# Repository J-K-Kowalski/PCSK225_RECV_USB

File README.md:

# PCSK225 RECEIVER WITH USB
## eCzas Radio PCSK-225 - Timeframe Receiver with USB

<ul>
<li>2024-07-25 - First version of the project</li>
</ul>

<p>Based on a receiver made of <a href="https://github.com/e-CzasPL/TimeReceiver225kHz" target="_blank">e-CzasPL Radio</a> I have developed a test receiver with a built-in serial/USB converter and a simple antenna amplifier on one transistor. The design is made in KiCAD 8.
</p>

<p>Receiver contains three basic blocks
<ol>
<li>USB interface on FT230X + LDO 3.3V
<li>DSPic33FJ128 processor with optional TCXO generator and PicDIV divider
<li>Radio interface on Si4735 chip with antenna amplifier on FET transistor
</ol> 

<b>NOTE</b> - The firmware comes from the eCzasPL project. I don't have the source codes.

### USB interface

<p>I built the USB interface on the FT230XS chip, one of the simplest serial/USB chips. I used a USB-C 2.0 connector for data transfer and a 5V power supply.
<p>To protect the circuit against reverse polarity (and such things happen in experiments), I used the Q2 transistor. Resistors R2 R3 inform the host computer that 5V is required. LED7 and LED8 show the transmission status.
<p> The U3 chip is a simple LDO with an output voltage of 3.3V. The whole circuit consumes about 100mA. This regulator, with a significant excess, provides such a current intensity. The external 3.3V power connector (when USB and LDO are not mounted) is protected by the Q4 transistor. The additional input of the 5V power supply is protected only by diode D1.

### DSPic33FJ128 processor

<p>Based on the eCzas original project, I used the DSPIC33FJ128MC804-PT processor indicated in the eCzasPL projections in an easy (relatively) manual mount housing. As standard, I included 100nF blocking capacitors on the appropriate pins, I2C pull-up resistors, and a quartz generator on a typical 10MHz quartz. The LED1 - LED4 LED set signals the status of the receiver. The device has two serial interfaces: NMEA and TEST. 
<p>The NMEA interface on pin (1) of the connector sends an NMEA frame $GPRMC - which allows the use of standard libraries available for microcontrollers and computers for time decoding. The second output, TEST on pin (3), sends information about the state of the chip in text form. Both interfaces operate at a speed of 115200 baud.
<p>Optionally, a high-precision TCXO generator can be installed, which generates a frequency of 10MHZ and can power the CPU clock. This significantly increases the accuracy of the work. To obtain a 1PPS signal, a PIC12F675 chip is used (in two versions of the housing, of course, only one of them needs to be installed). PICDIV source: http://www.leapsecond.com/pic/picdiv.htm, assembler & build-instructions: https://github.com/aewallin/PICDIV.

<p> NOTE - micro-stepping and PICDIV synchronization still need to be implemented in the eCzasPL Radio firmware.

### HF Receiver

<p>Ferrite antenna, e.g., from https://telzam.pl/anteny-dcf/ (also made by antennas at 225kHz), is connected via the ANT0 connector to the FET transistor, which acts as an amplifier. It is optional, and it is possible to short-circuit the appropriate JP2 fields so that the signal reaches the input of the Si4735 chip directly. This circuit is combined with a 32kHz watch quartz, which, using the SSB patch, allows for a mixed sideband frequency (upper USB) of 1kHz. This signal obtained from the LOUT output is amplified in a single-stage U$1A amplifier, and the signal feeds the processor's ADC. I used the second amplifier of the U$1B circuit as a 1kHz signal comparator.

### Output signals

<p>The NMEA output should have data as shown below. After getting synchronized, it appears every 1 minute. In frame $PGGUM, the first 9 bytes are the same as the encoded time frame, and the last is the time since the last received valid frame. An RMC (Recommended Minimum Specific GNSS Data) frame was used to synchronize the time. The receiver does not know its geographical location, so for compatibility with GNSS receivers, static coordinates are sent in the frame <a href="https://www.google.pl/maps/place/52%C2%B014'30.6%22N+21%C2%B000'03.0%22E/@52.24183,20.9982597,17z/data=!3m1!4b1!4m4!3m3!8m2!3d52.24183!4d21.00084?entry=ttu" target=_blank>Laboratory of Time and Frequency of the Central Office of Measures in Warsaw (52.24183N,  21.00084E)</a>.

<p>A detailed description is provided in <a href="https://github.com/e-CzasPL/TimeReceiver225kHz/blob/main/doc/e-CzasPL-Opis-projektu-przykladowego-modulu-odbiorczego-e-Czas-Radio.pdf">documentation</a> on page 8.

<p>

<p> On the TEST output, the system sends diagnostic data. STS: MAX/MIN - maximum and minimum level with ADC (12 bit) - can help optimize the 1 kHz audio level per CPU input. IIR - is "offset" - shifting the 1kHz fringe - from the nominal frequency, showing the "detuning" of the front end - controlled by this small quartz.  This allows the DSP filter to keep up with the usable signal. 
<p>

## LED Signals
<ul>
<li>LED1 - DCD Blue - signaling of recognition of the beginning of the data frame (after the keyword is detected) – remains lit until the end of the frame transmission,
<li>LED2 - RTC Green - Informs about receiving the correct time and entering it into the RTC, if it is not possible to update the RTC from the radio transmission, the diode is turned off after 24 hours,
<li>LED3 - PPS Yellow - 1PPS 1PPS signal synchronized with the received time signal,
<li>LED4 - FRM Orange - lit after the correct reception of the data frame, calculation of correction codes and confirmation of data correctness. The rising edge informs about the beginning of the second (transmitted in the data frame).
</ul>

# PCSK225 ODBIORNIK Z USB
## eCzas Radio PCSK-225 - Odbiornik ramki czasu z USB

<p> Na bazie odbiornika uroszczonego z <a href="https://github.com/e-CzasPL/TimeReceiver225kHz" target="_blank">e-CzasPL Radio</a> opracowałem testowy odbiornik z wbudowanym konwerterem serial/USB oraz prostym wzmacniaczem antenowym na jednym tranzystorze. Projekt jest wykonany w KiCAD 8.
</p>

<p>Odbiornik zawiera trzy podstawowe bloki
<ol>
<li>Interfejs USB na układzie FT230X + LDO 3.3V
<li>Procesor DSPic33FJ128 wraz z opcjonalnym generatorem TCXO i dzielnikiem PicDIV
<li>Interfejsem radiowym na układzie Si4735 ze wzmacniaczem antenowym na tranzystorze FET
</ol>

<b>UWAGA</b> - Firmware pochodzi z projektu eCzasPL, nie posiadam kodów źródłowych

### Interfejs USB

<p>Interfejs USB zbudowałem na układzie FT230XS, jednym z najprostszych układów typu serial/USB. Zastosowałem typowe złącze USB-C 2.0 do przesyłania danych i zasilania napięciem 5V.
<p>Do zabezpieczenia układu przed odwrotną polaryzacją (a takie rzeczy się zdarzają przy eksperymentach) zastosowałem tranzystor Q2. Rezystory R2, R3 informują komputer hosta że wymagane jest napięcie 5V. stan transmisji pokazują diody LED7 i LED8.
<p> Układ U3 jest prostym LDO o napięciu wyjściowym 3.3V. Cały układ pobiera ok 100mA, ten stabilizator z dużym  nadmiarem zapewnia takie natężenie prądu. Złącze zewnętrznego zasilania 3.3V (gdy nie jest zamontowany USB i LDO) jest zabezpieczone tranzystorem Q4. Wejście dodatkowe zasilania 5V zabezpieczone jest tylko diodą D1.

### Procesor DSPic33FJ128

<p>W układzie zastosowałem wskazany w projekcje eCzasPL procesor DSPIC33FJ128MC804-PT w łatwej (stosunkowo) do montażu ręcznego obudowie. Standardowo dołączyłem kondensatory blokujące 100nF na odpowiednich pinach, rezystory podciągające I2C, generator kwarcowy na typowym kwarcu 10MHz. Zestaw ledów LED1 - LED4 sygnalizuje status odbiornika. Układ ma dwa interfejsy szeregowe: NMEA i TEST. 
<p>Interfejs NMEA na pinie (1) złącza wysyła ramkę NMEA $GPRMC - co pozwoliło na stosowania do dekodowania czasu standardowych bibliotek dostępnych dla mikrokontrolerów i komputerów. Drugie wyjście TEST na pinie (3) wysyła informacje o stanie układu w postaci tekstowej. Obydwa interfejsy pracują w szybkości 115200 bodów.
<p>Opcjonalnie można zamontować precyzyjny generator TCXO który generuje częstotliwość 10MHZ i może zasilać zegar procesora. Znacznie zwiększa to dokładność pracy. W celu uzyskania sygnału 1PPS zastosowano układ PIC12F675 (w dwóch wersjach obudowy, oczywiście nalezy zamontować tylko jeden z nich). Kod źródłowy PICDIV: http://www.leapsecond.com/pic/picdiv.htm, assembler & build-instructions: https://github.com/aewallin/PICDIV.
	
<p> UWAGA - microsteping i synchronizacja PICDIV nie jest jeszcze zaimplementowana w firmware eCzasPL Radio.

### Odbiornik HF

<p>Antena ferrytowa np. z https://telzam.pl/anteny-dcf/ (wykonują także anteny na 225kHz) podłączona jest przez złącze ANT0 do tranzystora FET który pełni rolę wzmacniacza. Jest on opcjonalny i można zewrzeć odpowiednie pola JP2 aby sygnał docierał bezpośrednio do wejścia układu Si4735. Układ ten jest połączony z kwarcem zegarkowym 32kHz, co przy użyciu patcha SSB pozwala na uzyskanie zmieszanej częstotliwości wstęgi bocznej (górnej USB) o częstotliwości 1kHz. Ten sygnał uzyskiwany z wyjścia LOUT jest wzmacniany w jednostopniowym wzmacniaczu U$1A i sygnał zasila przetwornik ADC w procesorze. Drugi wzmacniacz układu U$1B użyłem jako komparator sygnału 1kHz.

### Sygnały wyjściowe

<p>Na wyjściu NMEA powinny byc dane jak pokazano poniżej. Po uzyskaniu synchronizacji pojawia się co 1min. ramka $PGGUM, pierwsze 9 bajtów to kojejne bajty zakodowanej ramki czasu, ostatni to czas od ostatnio odebranej poprawnej ramki. Do synchronizacji czasu zastosowano ramkę RMC (Recommended Minimum Specific GNSS Data). Odbiornik nie zna swojego położenia geograficznego, dlatego dla zachowania kompatybilności z odbiornikami GNSS w ramce przesyłane są statyczne współrzędne <a  href="https://www.google.pl/maps/place/52%C2%B014'30.6%22N+21%C2%B000'03.0%22E/@52.24183,20.9982597,17z/data=!3m1!4b1!4m4!3m3!8m2!3d52.24183!4d21.00084?entry=ttu" target=_blank>Laboratorium Czasu i Częstotliwości Głównego Urzędu Miar w Warszawie (52.24183N, 21.00084E)</a>.

<p>Dokładny opis zawarty jest w <a href="https://github.com/e-CzasPL/TimeReceiver225kHz/blob/main/doc/e-CzasPL-Opis-projektu-przykladowego-modulu-odbiorczego-e-Czas-Radio.pdf">dokumentacji</a>  na stronie 8.

<p>

<p> Na wyjściu TEST układ wysyła dane diagnostyczne. STS: MAX/MIN - maksymalny i minimalny poziom z ADC (12 bitów) - może być pomocny przy optymalizacji poziomu audio 1 kHz na wejście procesora. IIR - to "offset" - przesunięcie prążka 1kHz - od częstotliwości nominalnej, pokazuje "odstrojenie" frontendu - sterowanego tym kwarcem zegarkowym.  Umożliwia to nadążenie filtrem DSP za sygnałem użytecznym. 
<p>

## Sygnały LED
<ul>
<li>LED1 - DCD Blue - sygnalizacja rozpoznania początku ramki danych (po wykryciu słowa kluczowego) – pozostaje zapalona do końca transmisji ramki,
<li>LED2 - RTC Green - Informuje o odebraniu poprawnego czasu i wpisaniu go do RTC, w przypadku braku możliwości aktualizacji RTC z transmisji radiowej dioda jest gaszona po 24 godzinach,
<li>LED3 - PPS Yellow - 1PPS Sygnał 1PPS zsynchronizowany z odebranym sygnałem czasu,
<li>LED4 - FRM Orange - zapalana po poprawnym odebraniu ramki danych, przeliczeniu kodów korekcyjnych oraz potwierdzeniu poprawności danych. Narastające zbocze informuje o początku sekundy (przesłanej w ramce danych).
</ul>

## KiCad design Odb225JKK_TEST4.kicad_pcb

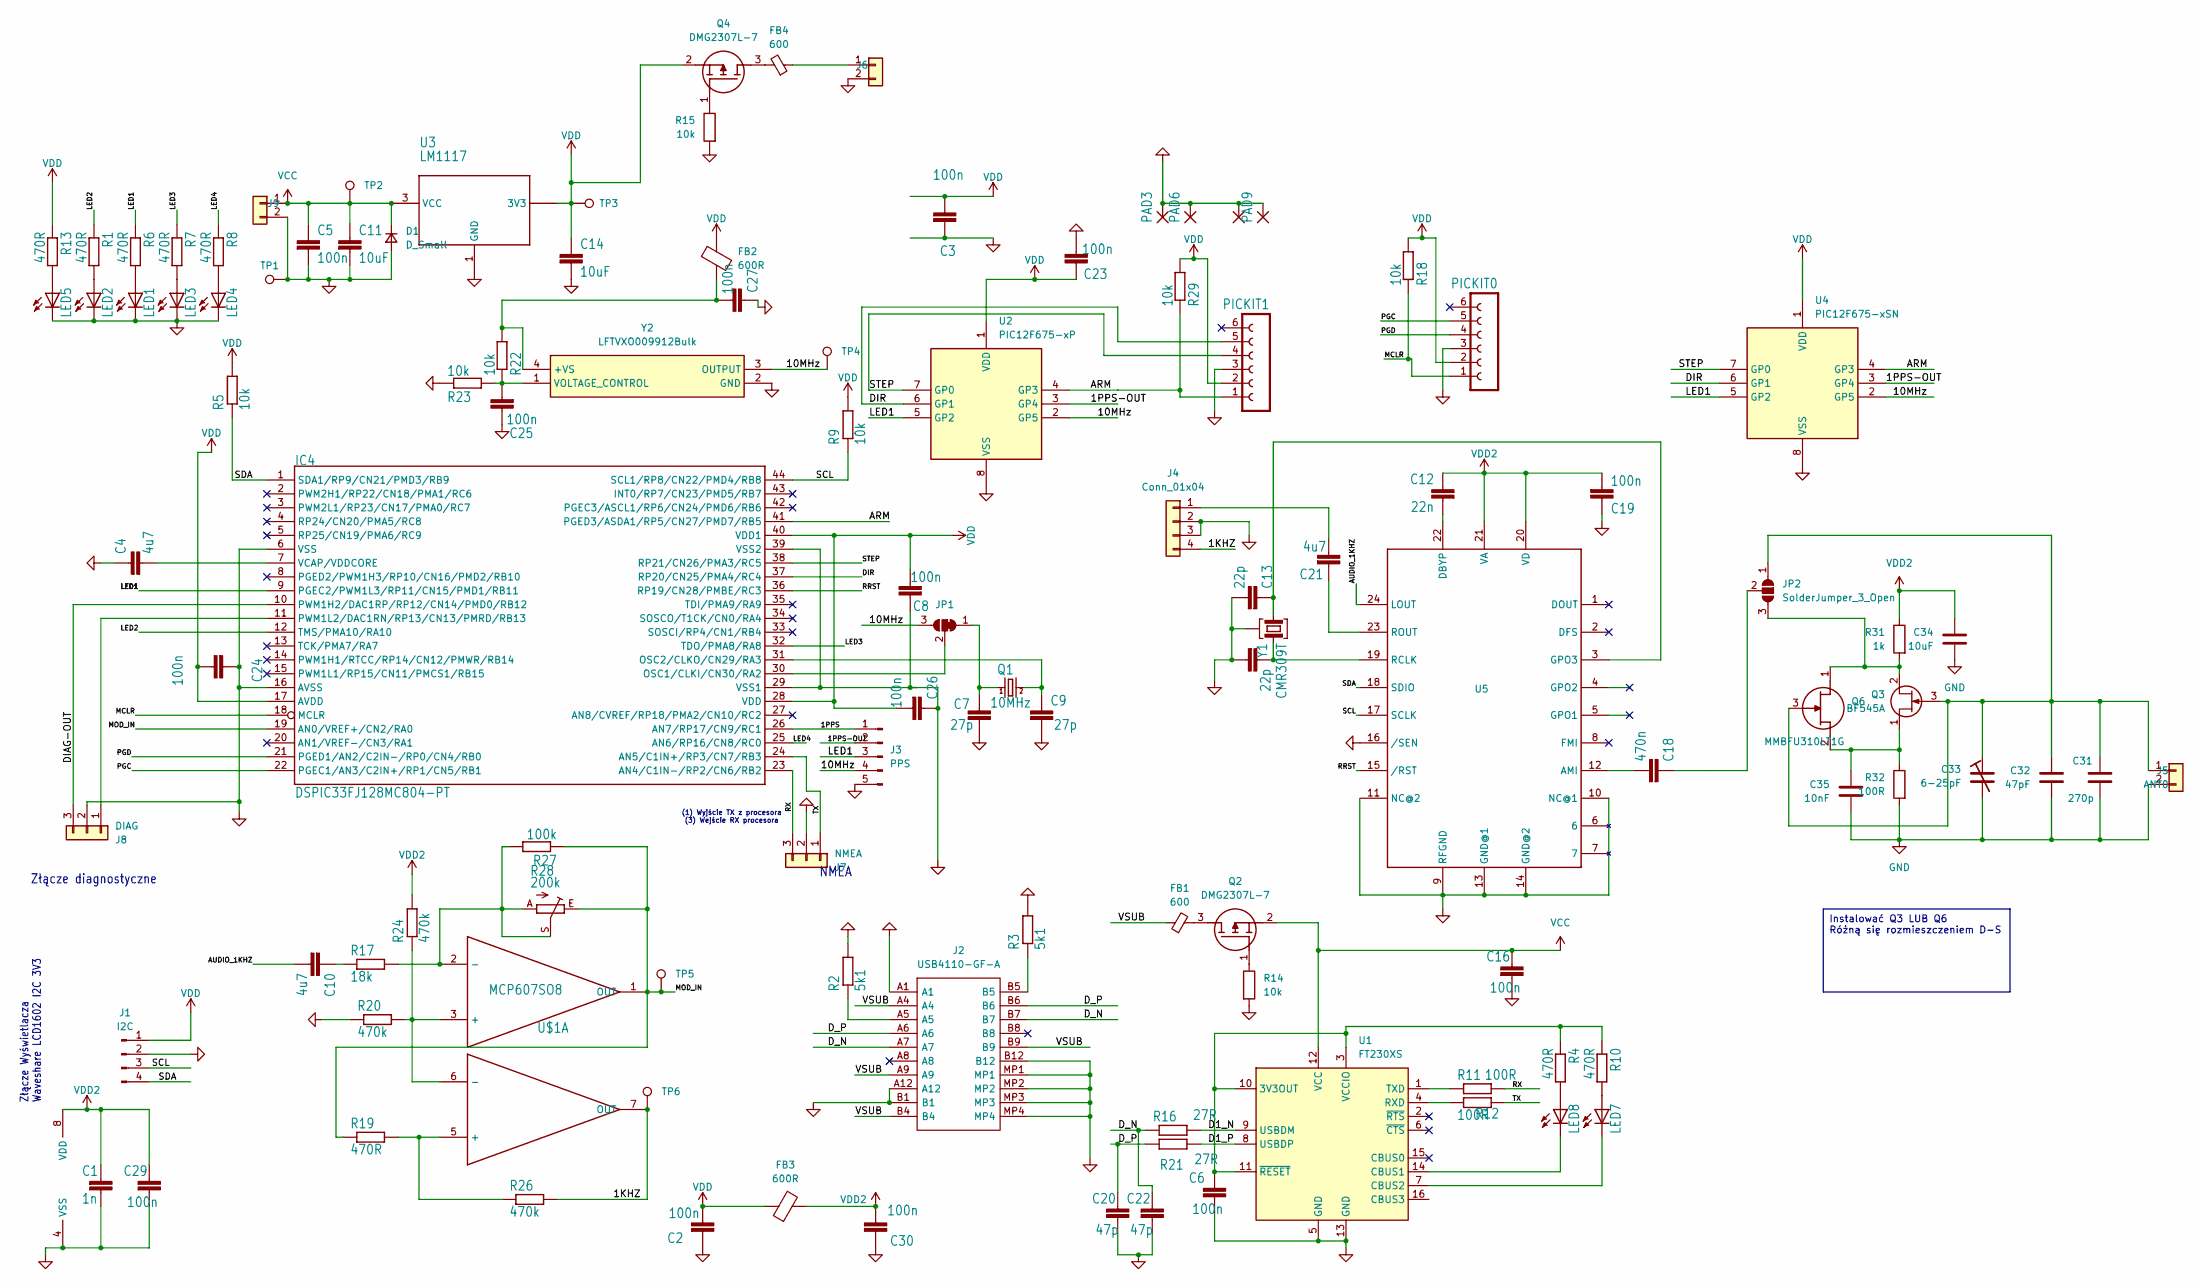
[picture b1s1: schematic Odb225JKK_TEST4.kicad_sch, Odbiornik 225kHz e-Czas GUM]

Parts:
C1: 1n; C_0603_1608Metric_Pad1.08x0.95mm_HandSolder
C2, C3, C5, C6, C8, C16, C19, C23, C24, C26, C27, C29, C30: 100n; C_0603_1608Metric_Pad1.08x0.95mm_HandSolder
C4, C10, C21: 4u7; C_0603_1608Metric_Pad1.08x0.95mm_HandSolder
C7, C9: 27p; C_0603_1608Metric_Pad1.08x0.95mm_HandSolder
C11, C14, C34: 10uF; C_0603_1608Metric_Pad1.08x0.95mm_HandSolder
C12: 22n; C_0603_1608Metric_Pad1.08x0.95mm_HandSolder
C13, C15: 22p; C_0603_1608Metric_Pad1.08x0.95mm_HandSolder
C18: 470n; C_0603_1608Metric_Pad1.08x0.95mm_HandSolder
C20, C22: 47p; C_0603_1608Metric_Pad1.08x0.95mm_HandSolder
C25: 100n; C0603K
C31: 270p; C_0603_1608Metric_Pad1.08x0.95mm_HandSolder
C32: 47pF; C_0603_1608Metric_Pad1.08x0.95mm_HandSolder
C33: 6-25pF; C_Trimmer_Murata_TZB4-B
C35: 10nF; C_0603_1608Metric_Pad1.08x0.95mm_HandSolder
D1: D_Small; D_1206_3216Metric_Pad1.42x1.75mm_HandSolder
FB1, FB4: 600; C0603K
FB2, FB3: 600R; C_0603_1608Metric_Pad1.08x0.95mm_HandSolder
IC4: DSPIC33FJ128MC804-PT; TQFP44
J1: I2C; PinHeader_1x04_P2.54mm_Vertical
J2: USB4110-GF-A; USB4110GFA; Mouser Part Number 640-USB4110-GF-A
J3: PPS; PinHeader_1x05_P2.54mm_Vertical
J4: Conn_01x04; PinHeader_1x04_P2.54mm_Vertical
J5, J6, J9: ANT0; PinHeader_1x02_P2.54mm_Vertical
J7: NMEA; PinHeader_1x03_P2.54mm_Vertical
J8: DIAG; PinHeader_1x03_P2.54mm_Vertical
JP1: SolderJumper_3_Bridged12; SolderJumper-3_P1.3mm_Bridged12_RoundedPad1.0x1.5mm
JP2: SolderJumper_3_Open; SolderJumper-3_P1.3mm_Open_RoundedPad1.0x1.5mm
LED1, LED2, LED3, LED4, LED5, LED7, LED8: LEDCHIPLED_0805; CHIP-LED0805
PAD3, PAD6, PAD8, PAD9: 1,6/0,9; 1,6_0,9
PICKIT0, PICKIT1: FE06-1; PinHeader_1x06_P2.54mm_Vertical
Q1: 10MHz; HC49U-V
Q2, Q4: DMG2307L-7; SOT96P240X110-3N; Mouser Part Number 621-DMG2307L-7
Q3: BF545A; SOT-23
Q6: MMBFU310LT1G; SOT96P237X111-3N; Mouser Part Number 863-MMBFU310LT1G
R1, R4, R6, R7, R8, R10, R13, R19: 470R; R_0603_1608Metric_Pad0.98x0.95mm_HandSolder
R2, R3: 5k1; R_0603_1608Metric_Pad0.98x0.95mm_HandSolder
R5, R9, R14, R15, R18, R22, R23, R29: 10k; R_0603_1608Metric_Pad0.98x0.95mm_HandSolder
R11, R12, R32: 100R; R_0603_1608Metric_Pad0.98x0.95mm_HandSolder
R16, R21: 27R; R_0603_1608Metric_Pad0.98x0.95mm_HandSolder
R17: 18k; R_0603_1608Metric_Pad0.98x0.95mm_HandSolder
R20, R24, R26: 470k; R_0603_1608Metric_Pad0.98x0.95mm_HandSolder
R27: 100k; R_0603_1608Metric_Pad0.98x0.95mm_HandSolder
R28: 200k; RJ9W
R31: 1k; R_0603_1608Metric_Pad0.98x0.95mm_HandSolder
TP1, TP2, TP3, TP4, TP5, TP6: TestPoint; TestPoint_Pad_D1.5mm
U1: FT230XS; SSOP-16_3.9x4.9mm_P0.635mm
U2: PIC12F675-xP; DIP-8_W7.62mm
U3: LM1117; SOT223-3
U4: PIC12F675-xSN; SOIC-8_3.9x4.9mm_P1.27mm
U5: SI4735-D60; SSOP24
U$1: MCP607SO8; SOIC8
Y1: CMR309T
Y2: LFTVXO009912Bulk; Mouser Part Number 449-LFTVXO009912BULK

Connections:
/1KHZ: J4.4, R26.2, TP6.1, U$1.7 (OUT)
/1PPS: IC4.26 (AN7/RP17/CN9/RC1), J3.1
/1PPS-OUT: J3.2, U2.3 (GP4), U4.3 (GP4)
/10MHz: J3.4, JP1.3 (B), TP4.1, U2.2 (GP5), U4.2 (GP5), Y2.3 (OUTPUT)
/ARM: IC4.41 (PGED3/ASDA1/RP5/CN27/PMD7/RB5), PICKIT1.1, R29.1, U2.4 (GP3), U4.4 (GP3)
/AUDIO_1KHZ: C10.2, U5.24 (LOUT)
/D1_N: R16.2, U1.9 (USBDM)
/D1_P: R21.2, U1.8 (USBDP)
/DIAG-OUT: IC4.10 (PWM1H2/DAC1RP/RP12/CN14/PMD0/RB12), J8.3
/DIR: IC4.37 (RP20/CN25/PMA4/RC4), PICKIT1.5, U2.6 (GP1), U4.6 (GP1)
/D_N: C22.1, J2.A7, J2.B7, R16.1
/D_P: C20.1, J2.A6, J2.B6, R21.1
/LED1: IC4.9 (PGEC2/PWM1L3/RP11/CN15/PMD1/RB11), J3.3, R6.1, U2.5 (GP2), U4.5 (GP2)
/LED2: IC4.12 (TMS/PMA10/RA10), R1.1
/LED3: IC4.32 (TDO/PMA8/RA8), R7.1
/LED4: IC4.25 (AN6/RP16/CN8/RC0), R8.1
/MCLR: IC4.18 (MCLR), PICKIT0.1, R18.1
/MOD_IN: IC4.19 (AN0/VREF+/CN2/RA0), R19.1, R27.1, R28.E, TP5.1, U$1.1 (OUT)
/PGC: IC4.22 (PGEC1/AN3/C2IN+/RP1/CN5/RB1), PICKIT0.5
/PGD: IC4.21 (PGED1/AN2/C2IN-/RP0/CN4/RB0), PICKIT0.4
/RRST: IC4.36 (RP19/CN28/PMBE/RC3), U5.15 (/RST)
/RX: IC4.23 (AN4/C1IN-/RP2/CN6/RB2), J7.3, R11.2
/SCL: IC4.44 (SCL1/RP8/CN22/PMD4/RB8), J1.3, R9.1, U5.17 (SCLK)
/SDA: IC4.1 (SDA1/RP9/CN21/PMD3/RB9), J1.4, R5.1, U5.18 (SDIO)
/STEP: IC4.38 (RP21/CN26/PMA3/RC5), PICKIT1.4, U2.7 (GP0), U4.7 (GP0)
/TX: IC4.24 (AN5/C1IN+/RP3/CN7/RB3), J7.1, R12.2
/VSUB: FB1.1, J2.A4, J2.A9, J2.B4, J2.B9
GND: C1.2, C2.2, C3.2, C4.1, C5.2, C6.2, C7.2, C8.1, C9.2, C11.2, C13.2, C14.2, C15.1, C16.2, C19.1, C20.2, C22.2, C23.2, C24.1, C25.1, C26.1, C27.1, C29.2, C30.2, C31.2, C32.2, C33.2, C34.2, C35.2, D1.2 (A), IC4.6 (VSS), IC4.16 (AVSS), IC4.29 (VSS1), IC4.39 (VSS2), J1.2, J2.A1, J2.A12, J2.B1, J2.B12, J2.MP1, J2.MP2, J2.MP3, J2.MP4, J3.5, J4.2, J4.3, J5.2, J6.2, J7.2, J8.2, J9.2, LED1.C, LED2.C, LED3.C, LED4.C, LED5.C, PAD3.1, PAD6.1, PAD8.1, PAD9.1, PICKIT0.3, PICKIT1.3, R2.2, R3.2, R14.2, R15.2, R20.1, R23.1, R32.2, TP1.1, U1.5 (GND), U1.13 (GND), U2.8 (VSS), U3.1 (GND), U4.8 (VSS), U5.9 (RFGND), U5.10 (NC@1), U5.11 (NC@2), U5.13 (GND@1), U5.14 (GND@2), U5.16 (/SEN), U$1.4 (VSS), Y1.3 (G), Y2.2 (GND)
unnamed: C10.1, R17.1
unnamed: IC4.30 (OSC1/CLKI/CN30/RA2), JP1.2 (C)
unnamed: C9.1, IC4.31 (OSC2/CLKO/CN29/RA3), Q1.2
unnamed: IC4.11 (PWM1L2/DAC1RN/RP13/CN13/PMRD/RB13), J8.1
unnamed: C4.2, IC4.7 (VCAP/VDDCORE)
unnamed: J2.A5, R2.1
unnamed: J2.B5, R3.1
unnamed: C21.2, J4.1
unnamed: C31.1, C32.1, C33.1, J5.1, JP2.1 (A), Q3.3 (G), Q6.3 (G)
unnamed: FB4.1, J6.1
unnamed: C7.1, JP1.1 (A), Q1.1
unnamed: JP2.3 (B), Q3.2 (D), Q6.1 (D), R31.2
unnamed: C18.1, JP2.2 (C)
unnamed: LED1.A, R6.2
unnamed: LED2.A, R1.2
unnamed: LED3.A, R7.2
unnamed: LED4.A, R8.2
unnamed: LED5.A, R13.2
unnamed: LED7.A, R10.2
unnamed: LED8.A, R4.2
unnamed: FB1.2, Q2.3 (D)
unnamed: Q2.1 (G), R14.1
unnamed: C35.1, Q3.1 (S), Q6.2 (S), R32.1
unnamed: FB4.2, Q4.3 (D)
unnamed: Q4.1 (G), R15.1
unnamed: C6.1, R4.1, R10.1, U1.3 (VCCIO), U1.10 (3V3OUT), U1.11 (~RESET)
unnamed: LED8.C, U1.14 (CBUS1)
unnamed: LED7.C, U1.7 (CBUS2)
unnamed: R12.1, U1.4 (RXD)
unnamed: R11.1, U1.1 (TXD)
unnamed: C18.2, U5.12 (AMI)
unnamed: C12.2, U5.22 (DBYP)
unnamed: C13.1, U5.3 (GPO3), Y1.1
unnamed: C15.2, U5.19 (RCLK), Y1.2
unnamed: C21.1, U5.23 (ROUT)
unnamed: R20.2, R24.1, U$1.3 (+), U$1.6 (-)
unnamed: R17.2, R27.2, R28.A, R28.S, U$1.2 (-)
unnamed: R19.2, R26.1, U$1.5 (+)
unnamed: C27.2, FB2.2, R22.2, Y2.4 (+VS)
unnamed: C25.2, R22.1, R23.2, Y2.1 (VOLTAGE_CONTROL)
VCC: C5.1, C11.1, C16.1, D1.1 (K), J9.1, Q2.2 (S), TP2.1, U1.12 (VCC), U3.3 (VCC)
VDD: C2.1, C3.1, C8.2, C14.1, C23.1, C24.2, C26.2, FB2.1, FB3.1, IC4.17 (AVDD), IC4.28 (VDD), IC4.40 (VDD1), J1.1, PICKIT0.2, PICKIT1.2, Q4.2 (S), R5.2, R9.2, R13.1, R18.2, R29.2, TP3.1, U2.1 (VDD), U3.2 (3V3), U3.4 (3V3), U4.1 (VDD)
VDD2: C1.1, C12.1, C19.2, C29.1, C30.1, C34.1, FB3.2, R24.2, R31.1, U5.20 (VD), U5.21 (VA), U$1.8 (VDD)

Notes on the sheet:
Instalować Q3 LUB Q6 Różną się rozmieszczeniem D-S
Złącze diagnostyczne
(1) Wyjście TX z procesora (3) Wejście RX procesora
Złącze Wyświetlacza Waveshare LCD1602 I2C 3V3
NMEA

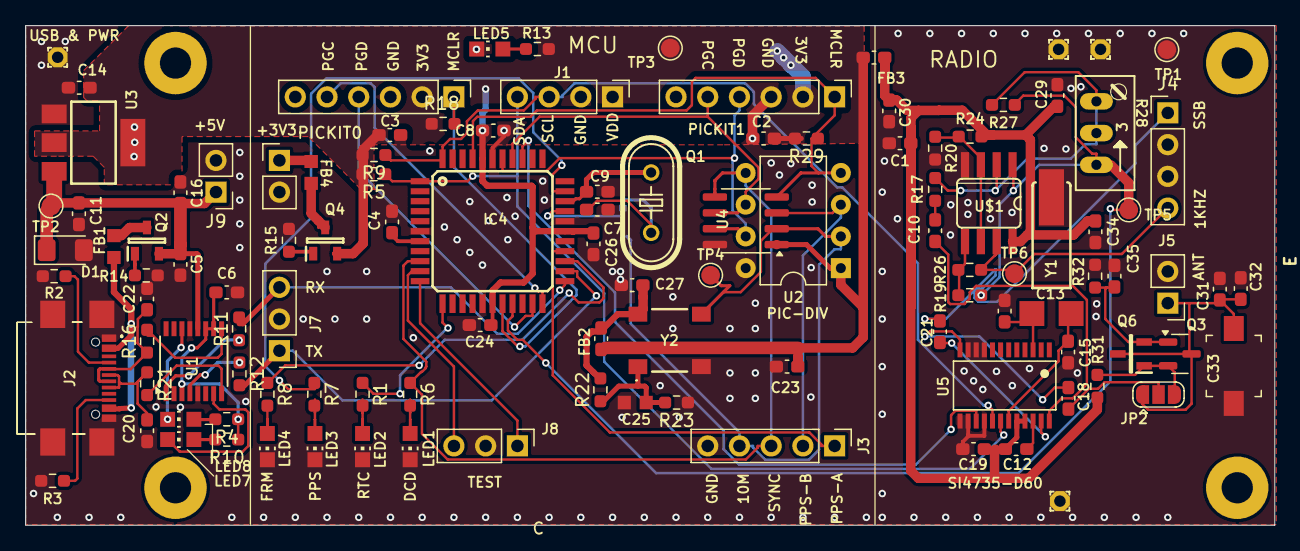
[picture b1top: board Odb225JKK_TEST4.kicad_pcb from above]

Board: 2 copper layers, 100.0 x 40.0 mm, 116 parts (1 on the bottom side), 71 nets.

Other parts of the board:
M1, M2, M3, M4: MountingHole_2.5mm_Pad

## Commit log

2024-07-25 initial files
2024-07-25 edit readme
2024-07-25 organize files

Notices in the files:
Odb225JKK_TEST4.kicad_pcb:
© JKK 2024.07
